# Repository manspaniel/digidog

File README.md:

# Digi-Dog

Lil digital dog for your pocket, for when you can't have a real dog (or when your real dog doesn't fit in your pocket).

## Work in Progress!

This project isn't finished yet! There's still plenty to do, but the basics are all there.

## PCB Files

Eagle files are provided in the `pcb` folder. I print the circuit board layout onto transparent A4 overhead projector material, then use pre-sensitised PCB boards + developer + chemical etchant to produce the boards. Watch [this video](https://www.youtube.com/watch?v=tWnfnt2rNO0) for the process I follow. It's easy once you have the stuff :)

This is my first PCB design. The layout is a bit shit, but that's ok.

## Uploading

I'm using Platform IO to manage platforms/libraries, and to upload compiled code to the ATTiny85. To program the chip, I'm using [https://www.sparkfun.com/products/11801](SparkFun Tiny Programmer), which is just great; you can program on the chip, or use breakout wires to program onto your soldered prototype. (I've added a breakout header row to my PCB for connecting the microcontroller to the programmer via some breadboard jumper wires).

## Tools

Comes with a custom-made sprite drawing program. To use:

```bash
> cd tools/sprite-draw
> npm install
> npm start
```

Documentation for the sprite drawing tool is [here](./tools/sprite-draw/README.md).

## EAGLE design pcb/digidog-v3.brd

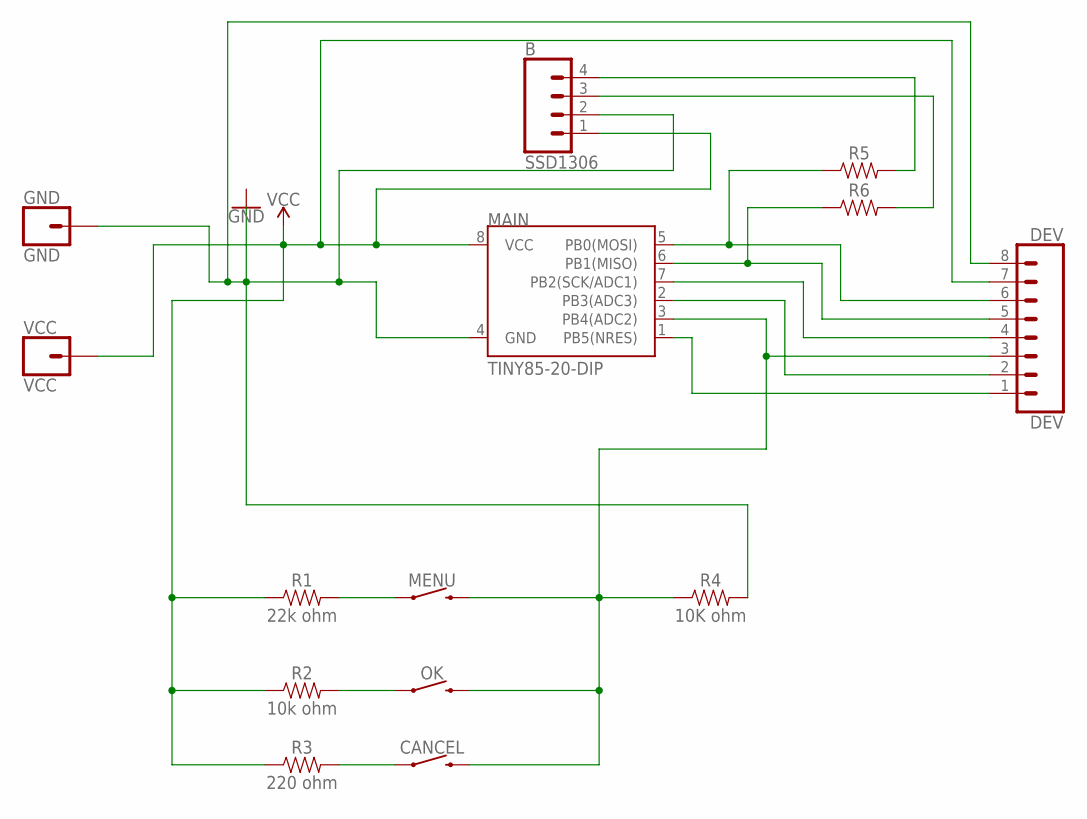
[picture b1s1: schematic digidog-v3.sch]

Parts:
B: SSD1306; 1X04
CANCEL: MOMENTARY-SWITCH-SPST-PTH-6.0MM; TACTILE_SWITCH_PTH_6.0MM
DEV: DEV; 1X08
GND: GND; 1X01
MAIN: TINY85-20-DIP; DIP08_MCU
MENU: MOMENTARY-SWITCH-SPST-PTH-6.0MM; TACTILE_SWITCH_PTH_6.0MM
OK: MOMENTARY-SWITCH-SPST-PTH-6.0MM; TACTILE_SWITCH_PTH_6.0MM
R1: 22k ohm; AXIAL-0.3
R2: 10k ohm; AXIAL-0.3
R3: 220 ohm; AXIAL-0.3
R4: 10K ohm; AXIAL-0.3
R5, R6: AXIAL-0.3
VCC: VCC; 1X01

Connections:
BUTTON: CANCEL.3 (2), DEV.3, MAIN.3 (PB4(ADC2)), MENU.3 (2), OK.3 (2), R4.P$1 (1)
GND: B.2, DEV.8, GND.1, MAIN.4 (GND), R4.P$2 (2)
unnamed: B.4, R5.P$2 (2)
unnamed: MENU.1, R1.P$2 (2)
unnamed: OK.1, R2.P$2 (2)
unnamed: CANCEL.1, R3.P$2 (2)
unnamed: DEV.6, MAIN.5 (PB0(MOSI)), R5.P$1 (1)
unnamed: DEV.5, MAIN.6 (PB1(MISO)), R6.P$1 (1)
unnamed: B.3, R6.P$2 (2)
unnamed: DEV.1, MAIN.1 (PB5(NRES))
unnamed: DEV.2, MAIN.2 (PB3(ADC3))
unnamed: DEV.4, MAIN.7 (PB2(SCK/ADC1))
VCC: B.1, DEV.7, MAIN.8 (VCC), R1.P$1 (1), R2.P$1 (1), R3.P$1 (1), VCC.1

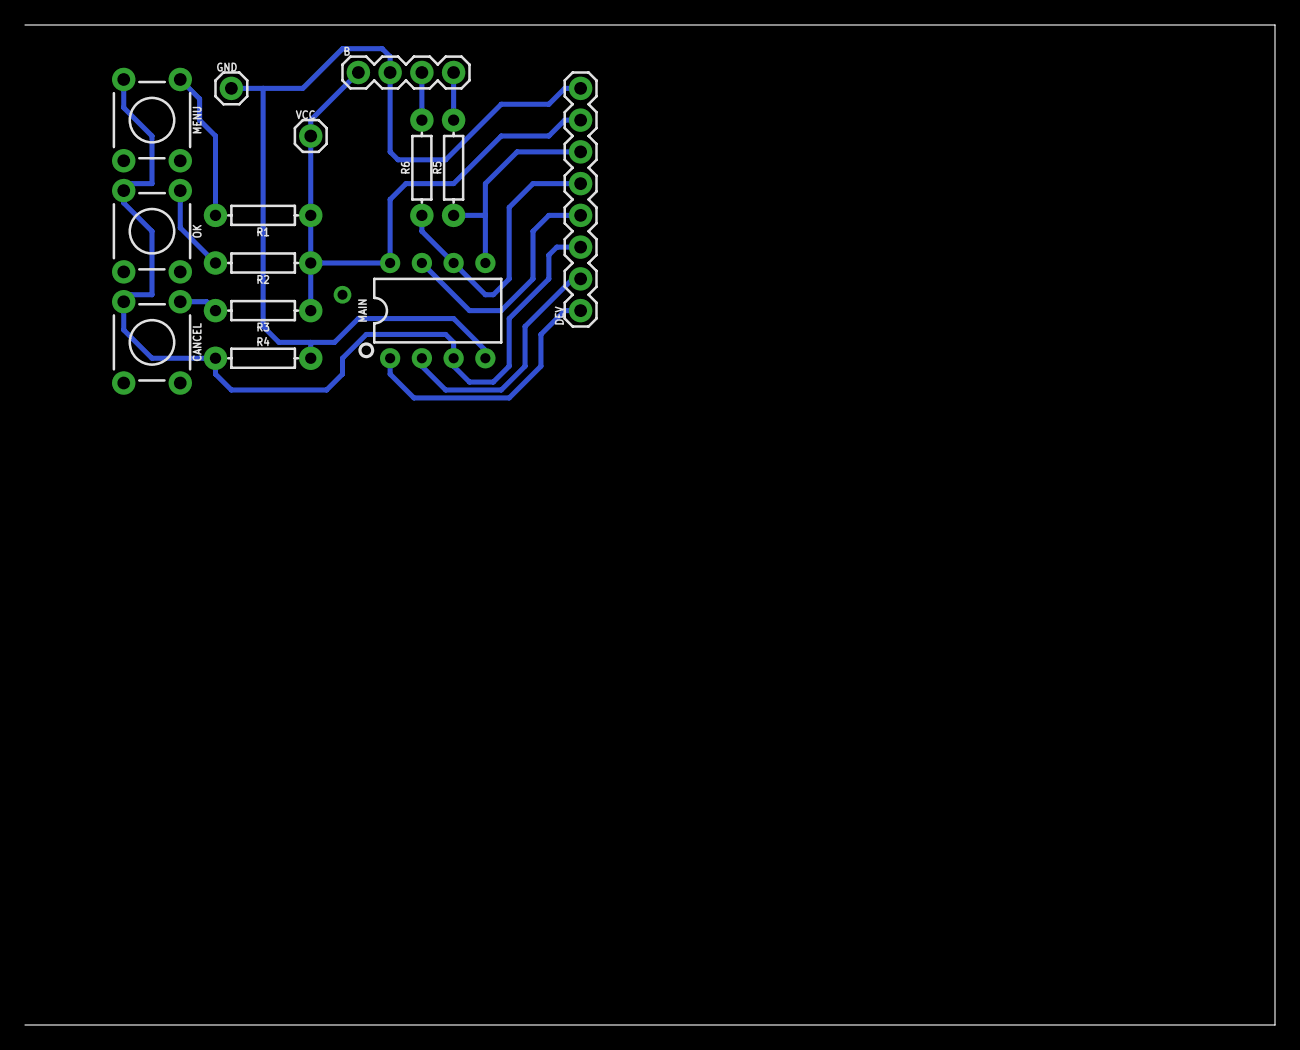
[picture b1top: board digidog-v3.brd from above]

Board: 2 copper layers, 100.0 x 80.0 mm, 14 parts (0 on the bottom side), 13 nets.

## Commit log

2017-08-09 Added README
2017-08-09 Can now swap sprite tiles by holding shift/ctrl/meta
2017-08-10 Added readme, added publishing and some keybaord shortcuts and bits
2017-08-30 Added eagle, changes to dog editor
2017-09-01 Added transparancy support
2017-09-02 Alpha sprites working vaguely, without alpha
2017-09-03 Automatic rendering of sprites
2017-09-03 Fixed bug with resizing sprites in editor. Fixed overdraw bug
2017-09-03 Dirtying screen segments now aligns correctly
2017-09-13 Added scene system
2017-10-12 Fixed init ram issue, added basic menu
2017-10-12 Code size optimisations

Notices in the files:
parts and their libraries:
SparkFun-Connectors: Licensing: Creative Commons ShareAlike 4.0 International - https://creativecommons.org/licenses/by-sa/4.0
